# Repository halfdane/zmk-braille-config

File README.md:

# Braille Keyboard
A 10 keys ortholinear mini-keyboard that connects via bluetooth.
Pressing the central six keys in braille patterns will send the corresponding keypresses to the host.

Find an example case in the directory [`case`](case)

## Features
- All german letters, numbers and symbols of grade 1
- Connects to up to five bluetooth hosts which can be changed on the fly
- [Haptic feedback](#haptic-feedback)
- Supports the complete german "Vollschrift" (i.e. grade 1): [patterns](de.md)
- Reset into bootloader mode for firmware updates
- Case can be 3D-printed
- rev2 (default) uses direct pin - so diodes aren't necessary for the matrix

## Missing Features
- No math mode
- No other languages
- Settings and Navigation etc. are confusing and undocumented

## Haptic Feedback
Uses the https://github.com/halfdane/zmk-behavior-haptic-feedback module to make a vibration motor go brr.

## Local development
Automatic setup expects you to run linux. 
On MacOS, it might just work with some changes, but you're on your own there.

`make west_setup` # this takes a while

Run `make` or `make all` to compile the firmware and copy it to your NICENANO.
`make clean` just removes the build dir, while `make deep_clean` removes all dependencies so you have to run `make west_setup` again.

`make follow` invokes the `tio` command to watch log messages fly by. It's lovely 🤗

## Roadmap
- build an MVC with
    - [x] xiao ble (instead of half broken nice!nano)
    - [x] 3d print a case (instead of using massive amounts of hot glue)
    - [x] a proper rumble motor (instead of soldering metal to the axis of a small motor)
    - [x] direct pin instead of a matrix (no diodes)
    - [x] batteries (instead of using a power bank because the loading circuit was fried years ago)
- try to combine the braille tables of liblouis with CLDR keyboard descriptions to automatically generate languages
- [x] activating the rumble motor is currently blocking the main thread - make it concurrent
- create a '1.0' version ("slimline")
    - smd components on a tiny pcb
    - repairable case (esp. openable)

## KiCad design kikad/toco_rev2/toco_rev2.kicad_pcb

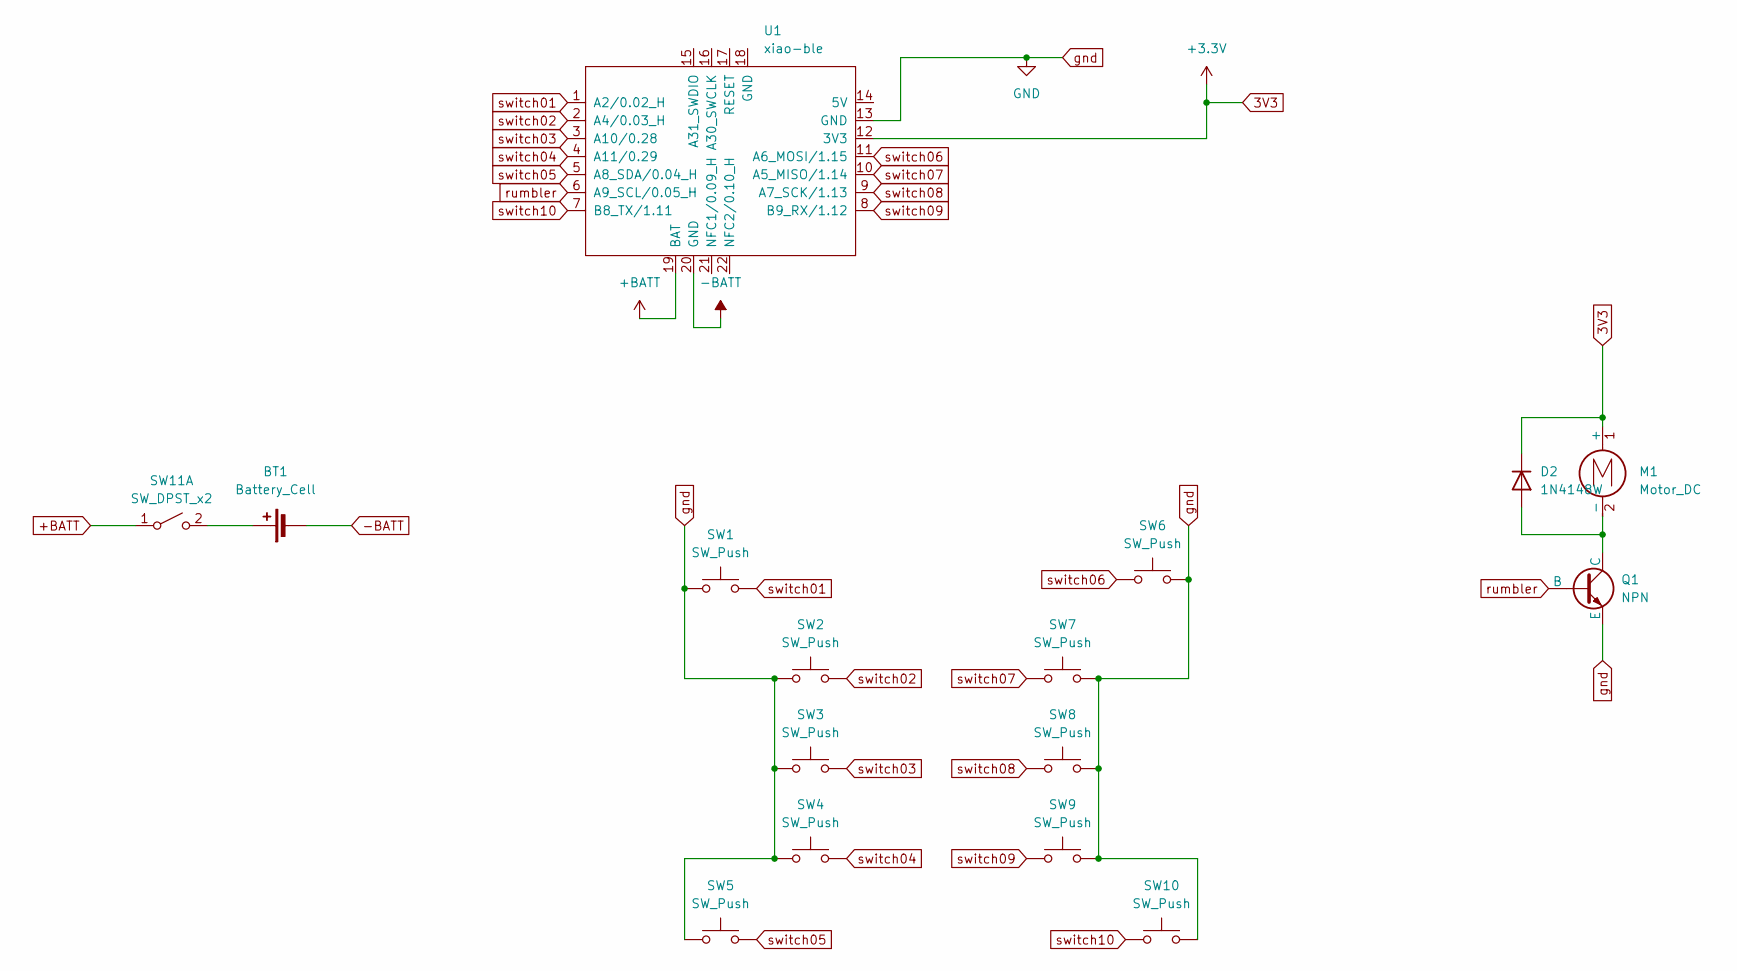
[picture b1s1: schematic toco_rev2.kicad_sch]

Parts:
BT1: Battery_Cell; SolderWire-0.5sqmm_1x02_P4.6mm_D0.9mm_OD2.1mm
D2: 1N4148W; D_SOD-123
M1: Motor_DC; SolderWire-0.5sqmm_1x02_P4.6mm_D0.9mm_OD2.1mm
Q1: NPN; SOT-23
SW1, SW2, SW3, SW4, SW5, SW6, SW7, SW8, SW9, SW10: SW_Push; SW_SPST_EVQP0
SW11: SW_DPST_x2; SW_SPDT_PCM12
U1: xiao-ble; xiao-ble-tht

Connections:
3V3: D2.1 (K), M1.1 (+), U1.12 (3V3)
+BATT: SW11.1 (A), U1.19 (BAT)
-BATT: BT1.2 (-), U1.20 (GND)
unnamed: BT1.1 (+), SW11.2 (B)
unnamed: D2.2 (A), M1.2 (-), Q1.1 (C)
gnd: Q1.3 (E), SW1.1, SW2.1, SW3.1, SW4.1, SW5.1, SW6.2, SW7.2, SW8.2, SW9.2, SW10.2, U1.13 (GND)
rumbler: Q1.2 (B), U1.6 (A9_SCL/0.05_H)
switch01: SW1.2, U1.1 (A2/0.02_H)
switch02: SW2.2, U1.2 (A4/0.03_H)
switch03: SW3.2, U1.3 (A10/0.28)
switch04: SW4.2, U1.4 (A11/0.29)
switch05: SW5.2, U1.5 (A8_SDA/0.04_H)
switch06: SW6.1, U1.11 (A6_MOSI/1.15)
switch07: SW7.1, U1.10 (A5_MISO/1.14)
switch08: SW8.1, U1.9 (A7_SCK/1.13)
switch09: SW9.1, U1.8 (B9_RX/1.12)
switch10: SW10.1, U1.7 (B8_TX/1.11)

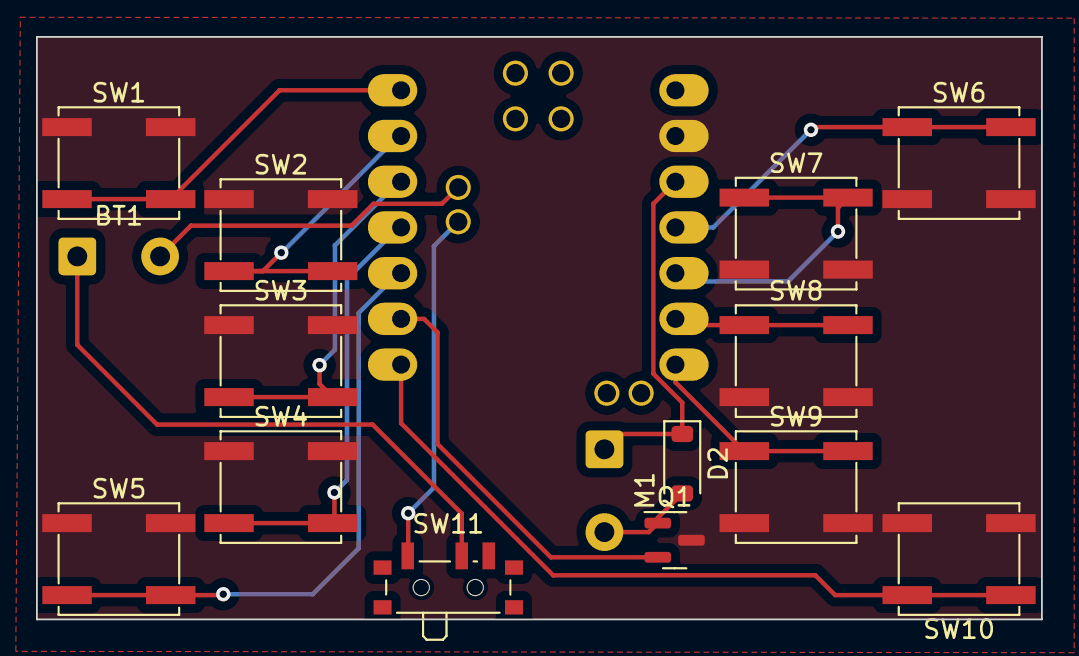
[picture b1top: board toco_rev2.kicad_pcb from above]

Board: 2 copper layers, 55.8 x 32.4 mm, 16 parts (0 on the bottom side), 17 nets.

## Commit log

2024-02-11 successfully build from source
2024-02-11 mapping of physical keys to positions is correct
2024-02-11 first tap dance and bootloader without pin shorting
2024-02-11 switch to correct layer when double tapping top right
2024-02-11 braille chars and some symbols
2024-02-11 layers don't work because combos use the physical position :/ but now numbers (mostly) work
2024-02-11 working with numbers, characters, simple expansions and some symbols.
2024-02-12 split definitions into include files
2024-02-12 include nodefree
2024-02-12 Revert "include nodefree"
    This reverts commit 0551bbb0e520ce3757fc59999de2ad490ce113dd.
2024-02-12 add nodefree without submodule
2024-02-12 symbols on android
2024-02-12 make keymap simpler
2024-02-13 some finetuning on timings and globals
2024-02-13 restructure
2024-02-14 put the nodeless macros somewhere else
2024-02-14 usintl done
2024-02-14 documentation
2024-02-14 de_de complete
2024-02-15 it's a rumbler, not a buzzer
2024-02-16 rumbling on ble_profile_change works
2024-02-16 use file from https://github.com/joelspadin/zmk-locale-generator instead of looking for the key combos individually
2024-02-16 remove comments
2024-02-16 starting to make it a real behavior
2024-02-20 use gpio instead of pwm for rumbler
2024-02-20 adjust special keys so they don't need multiple taps anymore. Add android navigation.
2024-02-21 make it a module instead of a config - hopefully that allows for implementing a behavior
2024-02-21 more experimentation between config and module
2024-02-21 this actually belongs to the previous commit
2024-02-21 adjust local build environment
2024-02-22 extract rumble into haptic feedback repo
2024-02-22 streamline makefile and add some documentation
2024-02-22 more doku
2024-02-23 add case
2024-02-23 add chamfer around usb. no idea what the other file is
2024-02-23 fix unclosed switch plate
2024-02-24 probably print ready
2024-02-24 fix weird glitch in slim case export
2024-02-24 add a model where mx switches don't interact with the case walls
2024-02-26 right side up
2024-02-27 prefer usb at the bottom
2024-02-27 adjust comment
2024-03-01 add more space for components
2024-03-01 remove obsolete STEP files
2024-03-01 export meshes for printing
2024-03-02 add a tester for switch holder
2024-03-02 add chamfer to *all* outer edges
2024-03-02 Adjust spacing around power switch
2024-03-04 integrate liblouis
2024-03-04 read liblouis tables
2024-03-04 add roadmap
2024-03-04 prepare for next version of braille keyboard
2024-03-04 add another version
2024-03-04 have two different versions
2024-03-04 cleaning up
2024-03-04 rename shield to Toco
2024-03-08 refactoring and reality check
2024-03-08 introducing rev2
2024-03-08 rev2 is reacting
2024-03-08 prevent continuous key repeats - add bootloader buttin
2024-03-08 advertise keyboard with correct name
2024-03-08 be able to clear all bluetooth pairings
2024-03-08 preserve current revision as 'initial' because it solves problems that'll probably arise again and again
2024-03-08 adjust keys layout
2024-03-11 make right half of switchplate identical to left part
2024-03-12 add correct pin layout
2024-03-14 fix local build from scratch
2024-03-14 add rumble feature to initial layout
2024-03-14 verify that the keyboard works
2024-03-14 documenting the schematic of revision 2
2024-03-14 adjust initial layout
2024-03-14 dot8 doesn't exist on revision 2
2024-03-14 can't #include conf files
2024-03-14 de_de works in rev2 same as rev1
2024-03-15 dot8 doesn't exist in rev2
2024-03-17 fiddling whith pcb
2024-03-17 automatic kicad backups
2024-03-19 user behavior definition from module
2024-03-19 documentation and cleanup
2024-07-13 upstream change in how to enable usb-logging. Nice thing is that it's only enabled in local builds
